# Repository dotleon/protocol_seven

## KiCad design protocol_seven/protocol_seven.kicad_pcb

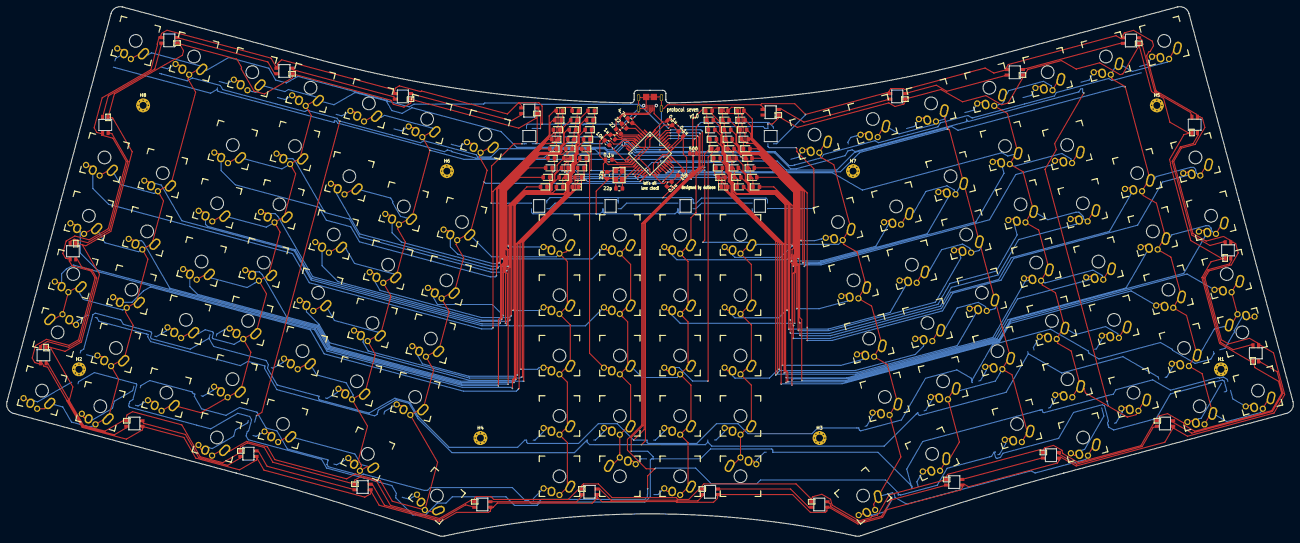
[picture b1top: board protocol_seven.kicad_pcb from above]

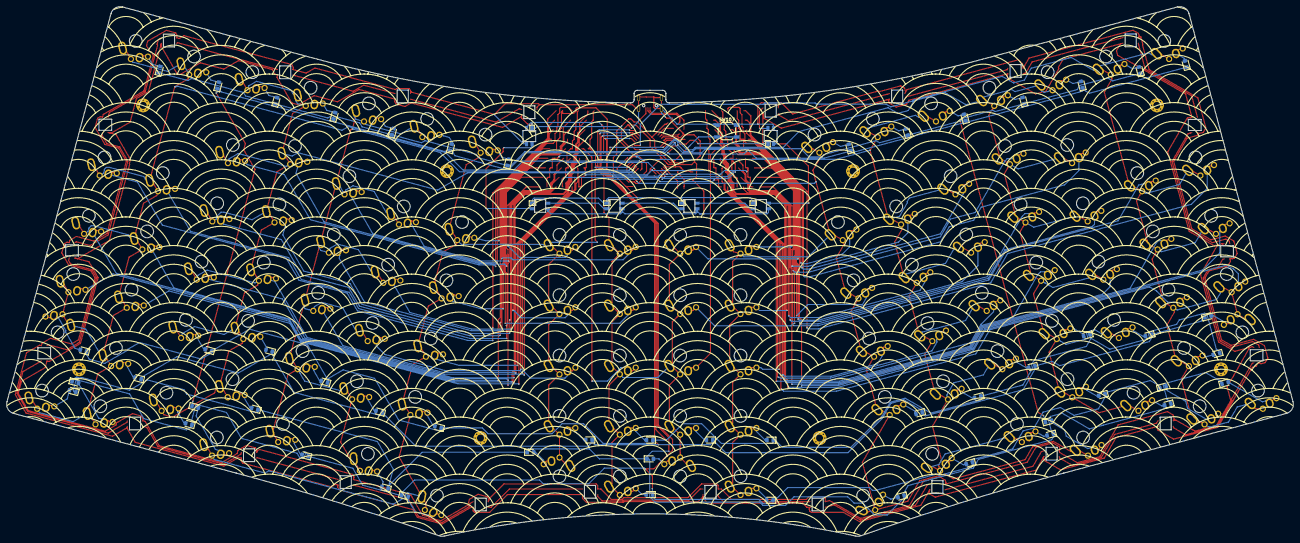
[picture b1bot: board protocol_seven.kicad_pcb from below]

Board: 2 copper layers, 405.1 x 166.8 mm, 267 parts (59 on the bottom side), 169 nets.

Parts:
C1: 1u; C_0805_2012Metric_Pad1.15x1.40mm_HandSolder
C2, C3: 22p; C_0805_2012Metric_Pad1.15x1.40mm_HandSolder
C4, C5, C6, C7: 0.1u; C_0805_2012Metric_Pad1.15x1.40mm_HandSolder
C8: 4.7u; C_0805_2012Metric_Pad1.15x1.40mm_HandSolder
D1, D2, D3, D4, D5, D6, D7, D8, D9, D10, D11, D12, D13, D14, D15, D16, D17, D18, D19, D20, D21, D22, D23, D24, D25, D26, D27, D28, D29, D30, D31, D32, D33, D34, D35, D36, D37, D38, D39, D40, D41, D42, D43, D44, D45, D46, D47, D48, D49, D50, D51, D52, D53, D54, D55, D56, D57, D58, D59, D60, D61, D62, D63, D64, D65, D66, D67, D68, D69, D70, D71, D72, D73, D74, D75, D76, D77, D78, D79, D80, D81, D82, D83, D84, D85, D86, D87, D88, D89, D90, D91, D92, D93, D94, D95, D96, D97, D98, D99, D100, D101, D102, D103, D104, D105, D106: D; D_0805_2012Metric_Pad1.15x1.40mm_HandSolder_nolabel
D107, D108, D109, D110, D111, D112, D113, D114, D115, D116, D117, D118, D119, D120, D121, D122, D123, D124, D125, D126, D127, D128, D129, D130, D131, D132, D133, D134, D135, D136: SK6812MINI; SK6812MINI_rev
H1, H2, H3, H4, H5, H6, H7, H8: Hole; MountingHole_2.2mm_M2_Pad_Via
J1: USB_mini_micro_B; aliexpress_microusb
R1, R2: 22; R_0805_2012Metric_Pad1.15x1.40mm_HandSolder
R3, R4: 10k; R_0805_2012Metric_Pad1.15x1.40mm_HandSolder
R5: 500; R_0805_2012Metric_Pad1.15x1.40mm_HandSolder
SW1, SW2, SW3, SW4, SW5, SW6, SW7, SW8, SW9, SW10, SW11, SW12, SW13, SW14, SW15, SW16, SW17, SW18, SW19, SW20, SW21, SW22, SW23, SW24, SW25, SW26, SW27, SW28, SW29, SW30, SW31, SW32, SW33, SW34, SW35, SW36, SW37, SW38, SW39, SW40, SW41, SW42, SW43, SW44, SW45, SW46, SW47, SW48, SW49, SW50, SW51, SW52, SW53, SW54, SW55, SW56, SW57, SW58, SW59, SW60, SW61, SW62, SW63, SW64, SW65, SW66, SW67, SW68, SW69, SW70, SW71, SW72, SW73, SW74, SW75, SW76, SW77, SW78, SW79, SW80, SW81, SW82, SW83, SW84, SW85, SW86, SW87, SW88, SW89, SW90, SW91, SW92, SW93, SW94, SW95, SW96, SW97, SW98, SW99, SW100, SW101, SW102, SW103, SW104, SW105, SW106: SW_Push; Kailh-Cherry-Hybrid-yoshi
SW107: SW_Push; SW_SPST_SKQG_WithStem
U1: ATMEGA32U4; ATMEGA32U4-AU
X1: XTAL_GND; FA-238-handsolder

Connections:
GND: C1.1, C2.2, C3.2, C4.1, C5.1, C6.1, C7.1, C8.1, D107.2, D108.2, D109.2, D110.2, D111.2, D112.2, D113.2, D114.2, D115.2, D116.2, D117.2, D118.2, D119.2, D120.2, D121.2, D122.2, D123.2, D124.2, D125.2, D126.2, D127.2, D128.2, D129.2, D130.2, D131.2, D132.2, D133.2, D134.2, D135.2, D136.2, J1.5, J1.6, R4.1, SW107.1, U1.5, U1.15, U1.23, U1.35, U1.43, X1.3
unnamed: C1.2, U1.6
unnamed: C2.1, U1.16, X1.1
unnamed: C3.1, U1.17, X1.2
unnamed: D1.2, SW1.2
unnamed: D2.2, SW2.2
unnamed: D3.2, SW3.2
unnamed: D4.2, SW4.2
unnamed: D5.2, SW5.2
unnamed: D6.2, SW6.2
unnamed: D7.2, SW7.2
unnamed: D8.2, SW8.2
unnamed: D9.2, SW9.2
unnamed: D10.2, SW10.2
unnamed: D11.2, SW11.2
unnamed: D12.2, SW12.2
unnamed: D13.2, SW13.2
unnamed: D14.2, SW14.2
unnamed: D15.2, SW15.2
unnamed: D16.2, SW16.2
unnamed: D17.2, SW17.2
unnamed: D18.2, SW18.2
unnamed: D19.2, SW19.2
unnamed: D20.2, SW20.2
unnamed: D21.2, SW21.2
unnamed: D22.2, SW22.2
unnamed: D23.2, SW23.2
unnamed: D24.2, SW24.2
unnamed: D25.2, SW25.2
unnamed: D26.2, SW26.2
unnamed: D27.2, SW27.2
unnamed: D28.2, SW28.2
unnamed: D29.2, SW29.2
unnamed: D30.2, SW30.2
unnamed: D31.2, SW31.2
unnamed: D32.2, SW32.2
unnamed: D33.2, SW33.2
unnamed: D34.2, SW34.2
unnamed: D35.2, SW35.2
unnamed: D36.2, SW36.2
unnamed: D37.2, SW37.2
unnamed: D38.2, SW38.2
unnamed: D39.2, SW39.2
unnamed: D40.2, SW40.2
unnamed: D41.2, SW41.2
unnamed: D42.2, SW42.2
unnamed: D43.2, SW43.2
unnamed: D44.2, SW44.2
unnamed: D45.2, SW45.2
unnamed: D46.2, SW46.2
unnamed: D47.2, SW47.2
unnamed: D48.2, SW48.2
unnamed: D49.2, SW49.2
unnamed: D50.2, SW50.2
unnamed: D51.2, SW51.2
unnamed: D52.2, SW52.2
unnamed: D53.2, SW53.2
unnamed: D54.2, SW54.2
unnamed: D55.2, SW55.2
unnamed: D56.2, SW56.2
unnamed: D57.2, SW57.2
unnamed: D58.2, SW58.2
unnamed: D59.2, SW59.2
unnamed: D60.2, SW60.2
unnamed: D61.2, SW61.2
unnamed: D62.2, SW62.2
unnamed: D63.2, SW63.2
unnamed: D64.2, SW64.2
unnamed: D65.2, SW65.2
unnamed: D66.2, SW66.2
unnamed: D67.2, SW67.2
unnamed: D68.2, SW68.2
unnamed: D69.2, SW69.2
unnamed: D70.2, SW70.2
unnamed: D71.2, SW71.2
unnamed: D72.2, SW72.2
unnamed: D73.2, SW73.2
unnamed: D74.2, SW74.2
unnamed: D75.2, SW75.2
unnamed: D76.2, SW76.2
unnamed: D77.2, SW77.2
unnamed: D78.2, SW78.2
unnamed: D79.2, SW79.2
unnamed: D80.2, SW80.2
unnamed: D81.2, SW81.2
unnamed: D82.2, SW82.2
unnamed: D83.2, SW83.2
unnamed: D84.2, SW84.2
unnamed: D85.2, SW85.2
unnamed: D86.2, SW86.2
unnamed: D87.2, SW87.2
unnamed: D88.2, SW88.2
unnamed: D89.2, SW89.2
unnamed: D90.2, SW90.2
unnamed: D91.2, SW91.2
unnamed: D92.2, SW92.2
unnamed: D93.2, SW93.2
unnamed: D94.2, SW94.2
unnamed: D95.2, SW95.2
unnamed: D96.2, SW96.2
unnamed: D97.2, SW97.2
unnamed: D98.2, SW98.2
unnamed: D99.2, SW99.2
unnamed: D100.2, SW100.2
unnamed: D101.2, SW101.2
unnamed: D102.2, SW102.2
unnamed: D103.2, SW103.2
unnamed: D104.2, SW104.2
unnamed: D105.2, SW105.2
unnamed: D106.2, SW106.2
unnamed: D107.1, D108.3
unnamed: D107.3, R5.2
unnamed: D108.1, D109.3
unnamed: D109.1, D110.3
unnamed: D110.1, D111.3
unnamed: D111.1, D112.3
unnamed: D112.1, D113.3
unnamed: D113.1, D114.3
unnamed: D114.1, D115.3
unnamed: D115.1, D116.3
unnamed: D116.1, D117.3
unnamed: D117.1, D118.3
unnamed: D118.1, D119.3
unnamed: D119.1, D120.3
unnamed: D120.1, D121.3
unnamed: D121.1, D122.3
unnamed: D122.1, D123.3
unnamed: D123.1, D124.3
unnamed: D124.1, D125.3
unnamed: D125.1, D126.3
unnamed: D126.1, D127.3
unnamed: D127.1, D128.3
unnamed: D128.1, D129.3
unnamed: D129.1, D130.3
unnamed: D130.1, D131.3
unnamed: D131.1, D132.3
unnamed: D132.1, D133.3
unnamed: D133.1, D134.3
unnamed: D134.1, D135.3
unnamed: D135.1, D136.3
unnamed: J1.2, R1.2
unnamed: J1.3, R2.2
unnamed: R1.1, U1.3
unnamed: R2.1, U1.4
unnamed: R3.1, SW107.2, U1.13
unnamed: R4.2, U1.33
unnamed: R5.1, U1.8
VCC: C4.2, C5.2, C6.2, C7.2, C8.2, D107.4, D108.4, D109.4, D110.4, D111.4, D112.4, D113.4, D114.4, D115.4, D116.4, D117.4, D118.4, D119.4, D120.4, D121.4, D122.4, D123.4, D124.4, D125.4, D126.4, D127.4, D128.4, D129.4, D130.4, D131.4, D132.4, D133.4, D134.4, D135.4, D136.4, J1.1, R3.2, U1.2, U1.7, U1.14, U1.24, U1.34, U1.44
col0: SW1.1, SW2.1, SW3.1, SW4.1, SW5.1, SW6.1, SW7.1, SW8.1, SW9.1, SW10.1, SW11.1, SW12.1, U1.37
col1: SW13.1, SW14.1, SW15.1, SW16.1, SW17.1, SW18.1, SW19.1, SW20.1, SW21.1, SW22.1, SW23.1, SW24.1, U1.36
col2: SW25.1, SW26.1, SW27.1, SW28.1, SW29.1, SW30.1, SW31.1, SW32.1, SW33.1, SW34.1, SW35.1, SW36.1, U1.32
col3: SW37.1, SW38.1, SW39.1, SW40.1, SW41.1, SW42.1, SW43.1, SW44.1, SW45.1, SW46.1, SW47.1, SW48.1, U1.31
col4: SW49.1, SW50.1, SW51.1, SW52.1, SW53.1, SW54.1, SW55.1, SW56.1, SW57.1, SW58.1, U1.30
col5: SW59.1, SW60.1, SW61.1, SW62.1, SW63.1, SW64.1, SW65.1, SW66.1, SW67.1, SW68.1, SW69.1, SW70.1, U1.29
col6: SW71.1, SW72.1, SW73.1, SW74.1, SW75.1, SW76.1, SW77.1, SW78.1, SW79.1, SW80.1, SW81.1, SW82.1, U1.28
col7: SW83.1, SW84.1, SW85.1, SW86.1, SW87.1, SW88.1, SW89.1, SW90.1, SW91.1, SW92.1, SW93.1, SW94.1, U1.27
col8: SW95.1, SW96.1, SW97.1, SW98.1, SW99.1, SW100.1, SW101.1, SW102.1, SW103.1, SW104.1, SW105.1, SW106.1, U1.26
row0: D1.1, D13.1, D25.1, D37.1, D59.1, D71.1, D83.1, D95.1, U1.9
row1: D7.1, D19.1, D31.1, D43.1, D65.1, D77.1, D89.1, D101.1, U1.10
row2: D2.1, D14.1, D26.1, D38.1, D49.1, D60.1, D72.1, D84.1, D96.1, U1.11
row3: D8.1, D20.1, D32.1, D44.1, D54.1, D66.1, D78.1, D90.1, D102.1, U1.18
row4: D3.1, D15.1, D27.1, D39.1, D50.1, D61.1, D73.1, D85.1, D97.1, U1.19
row5: D9.1, D21.1, D33.1, D45.1, D55.1, D67.1, D79.1, D91.1, D103.1, U1.20
row6: D4.1, D16.1, D28.1, D40.1, D51.1, D62.1, D74.1, D86.1, D98.1, U1.21
row7: D10.1, D22.1, D34.1, D46.1, D56.1, D68.1, D80.1, D92.1, D104.1, U1.22
row8: D5.1, D17.1, D29.1, D41.1, D52.1, D63.1, D75.1, D87.1, D99.1, U1.41
row9: D11.1, D23.1, D35.1, D47.1, D57.1, D69.1, D81.1, D93.1, D105.1, U1.40
row10: D6.1, D18.1, D30.1, D42.1, D53.1, D64.1, D76.1, D88.1, D100.1, U1.39
row11: D12.1, D24.1, D36.1, D48.1, D58.1, D70.1, D82.1, D94.1, D106.1, U1.38
